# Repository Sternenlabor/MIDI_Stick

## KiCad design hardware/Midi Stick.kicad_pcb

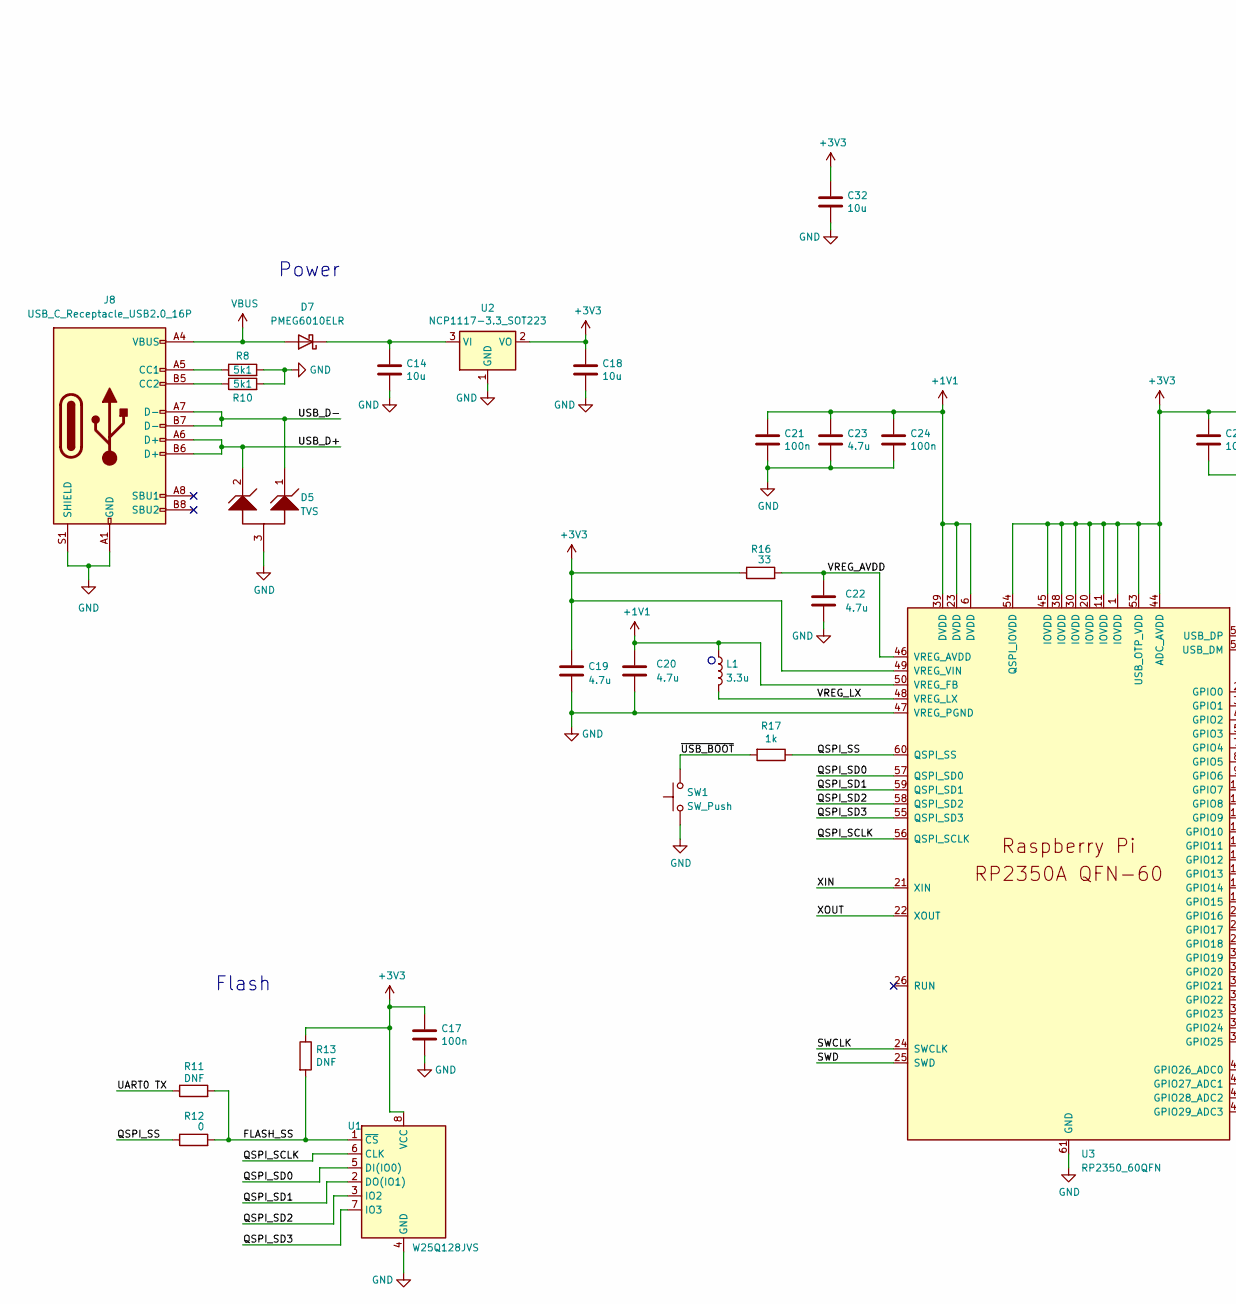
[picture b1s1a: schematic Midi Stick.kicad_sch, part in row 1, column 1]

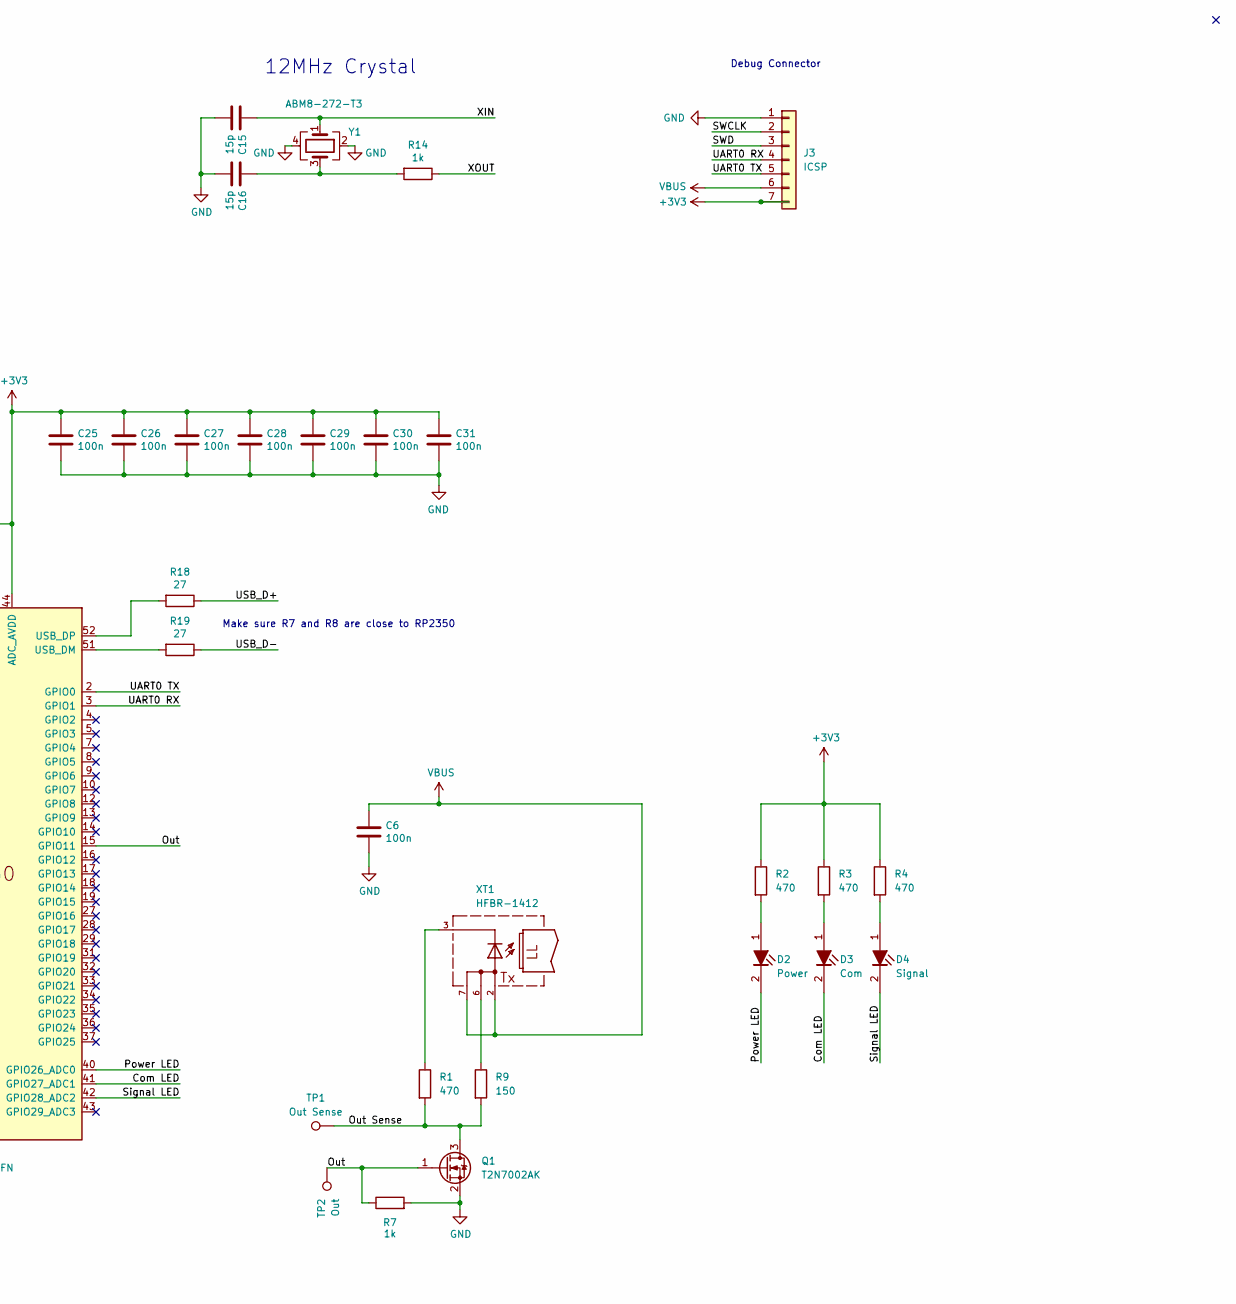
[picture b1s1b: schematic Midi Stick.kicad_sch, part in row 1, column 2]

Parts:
C6, C17, C21, C24, C25, C26, C27, C28, C29, C30, C31: 100n; C_0402_1005Metric
C14, C18, C32: 10u; C_0805_2012Metric
C15, C16: 15p; C_0402_1005Metric
C19, C20, C22, C23: 4.7u; C_0402_1005Metric
D2: Power; LED_0603_1608Metric
D3: Com; LED_0603_1608Metric
D4: Signal; LED_0603_1608Metric
D5: TVS; SOT95P230X110-3N
D7: PMEG6010ELR; D_SOD-123F
J3: ICSP; PinSocket_1x07_P2.54mm_Vertical
J8: USB_C_Receptacle_USB2.0_16P; USB_C_Receptacle_GCT_USB4105-xx-A_16P_TopMnt_Horizontal
L1: 3.3u; L_pol_2016
Q1: T2N7002AK; SOT-23
R1, R2, R3, R4: 470; R_0402_1005Metric
R7, R14, R17: 1k; R_0402_1005Metric
R8, R10: 5k1; R_0402_1005Metric
R9: 150; R_0402_1005Metric
R11, R13: DNF; R_0402_1005Metric
R12: 0; R_0402_1005Metric
R16: 33; R_0402_1005Metric
R18, R19: 27; R_0402_1005Metric
SW1: SW_Push; SW_Push_1P1T_NO_Vertical_Wuerth_434133025816
TP1: Out Sense; TestPoint_Pad_1.0x1.0mm
TP2: Out; PinHeader_1x01_P2.54mm_Vertical
U1: W25Q128JVS; SOIC-8_5.23x5.23mm_P1.27mm
U2: NCP1117-3.3_SOT223; SOT-223-3_TabPin2
U3: RP2350_60QFN; RP2350-QFN-60-1EP_7x7_P0.4mm_EP3.4x3.4mm_ThermalVias
XT1: HFBR-1412; HFBR-X41X; MPN HFBR-1412
Y1: ABM8-272-T3; Crystal_SMD_3225-4Pin_3.2x2.5mm

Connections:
+1V1: C20.1, C21.1, C23.1, C24.1, L1.1, U3.6 (DVDD), U3.23 (DVDD), U3.39 (DVDD), U3.50 (VREG_FB)
+3V3: C17.1, C18.1, C19.1, C25.1, C26.1, C27.1, C28.1, C29.1, C30.1, C31.1, C32.1, J3.7, R2.1, R3.1, R4.1, R13.1, R16.1, U1.8 (VCC), U2.2 (VO), U3.1 (IOVDD), U3.11 (IOVDD), U3.20 (IOVDD), U3.30 (IOVDD), U3.38 (IOVDD), U3.44 (ADC_AVDD), U3.45 (IOVDD), U3.49 (VREG_VIN), U3.53 (USB_OTP_VDD), U3.54 (QSPI_IOVDD); also elsewhere on the board
/Com LED: D3.2, U3.41 (GPIO27_ADC1)
/FLASH_SS: R11.2, R12.2, R13.2, U1.1 (~CS)
/Out: Q1.1 (G), R7.1, TP2.1, U3.15 (GPIO11)
/Out Sense: Q1.3 (D), R1.2, R9.2, TP1.1
/Power LED: D2.2, U3.40 (GPIO26_ADC0)
/QSPI_SCLK: U1.6 (CLK), U3.56 (QSPI_SCLK)
/QSPI_SD0: U1.5 (DI(IO0)), U3.57 (QSPI_SD0)
/QSPI_SD1: U1.2 (DO(IO1)), U3.59 (QSPI_SD1)
/QSPI_SD2: U1.3 (IO2), U3.58 (QSPI_SD2)
/QSPI_SD3: U1.7 (IO3), U3.55 (QSPI_SD3)
/QSPI_SS: R12.1, R17.1, U3.60 (QSPI_SS)
/SWCLK: J3.2, U3.24 (SWCLK)
/SWD: J3.3, U3.25 (SWD)
/Signal LED: D4.2, U3.42 (GPIO28_ADC2)
/UART0 RX: J3.4, U3.3 (GPIO1)
/UART0 TX: J3.5, R11.1, U3.2 (GPIO0)
/USB_D+: D5.2 (19), J8.A6 (D+), J8.B6 (D+), R18.1
/USB_D-: D5.1 (18), J8.A7 (D-), J8.B7 (D-), R19.1
/VREG_AVDD: C22.1, R16.2, U3.46 (VREG_AVDD)
/VREG_LX: L1.2, U3.48 (VREG_LX)
/XIN: C15.1, U3.21 (XIN), Y1.1
/XOUT: R14.1, U3.22 (XOUT)
/~USB_BOOT: R17.2, SW1.2
GND: C6.2, C14.2, C15.2, C16.2, C17.2, C18.2, C19.2, C20.2, C21.2, C22.2, C23.2, C24.2, C25.2, C26.2, C27.2, C28.2, C29.2, C30.2, C31.2, C32.2, D5.3 (20), J3.1, J8.A1 (GND), J8.A12 (GND), J8.B1 (GND), J8.B12 (GND), J8.S1 (SHIELD), Q1.2 (S), R7.2, R8.2, R10.2, SW1.1, U1.4 (GND), U2.1 (GND), U3.47 (VREG_PGND), U3.61 (GND), Y1.2, Y1.4; also elsewhere on the board
unnamed: C16.1, R14.2, Y1.3
unnamed: D2.1, R2.2
unnamed: D3.1, R3.2
unnamed: D4.1, R4.2
unnamed: C14.1, D7.1 (K), U2.3 (VI)
unnamed: J8.A5 (CC1), R8.1
unnamed: J8.B5 (CC2), R10.1
unnamed: R1.1, XT1.3
unnamed: R9.1, XT1.6
unnamed: R19.2, U3.51 (USB_DM)
unnamed: R18.2, U3.52 (USB_DP)
VBUS: C6.1, D7.2 (A), J3.6, J8.A4 (VBUS), J8.A9 (VBUS), J8.B4 (VBUS), J8.B9 (VBUS), XT1.2, XT1.7

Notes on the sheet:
Debug Connector
Make sure R7 and R8 are close to RP2350
Power
Flash
12MHz Crystal

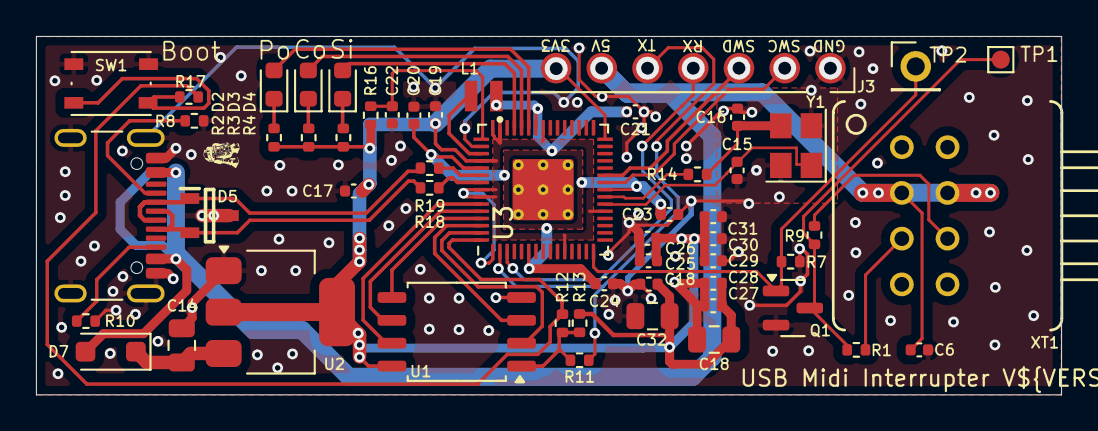
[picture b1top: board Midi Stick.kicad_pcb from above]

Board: 2 copper layers, 57.0 x 19.9 mm, 54 parts (0 on the bottom side), 38 nets.

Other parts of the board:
C18#2: 100n; C_0402_1005Metric

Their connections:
+3V3: C18#2.1; also elsewhere on the board
GND: C18#2.2; also elsewhere on the board

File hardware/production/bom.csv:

Designator,Footprint,Quantity,Value,LCSC Part #
"C14, C18_2, C32",0805,3,10u,
"C15, C16",0402,2,15p,
"C17, C18, C21, C24, C25, C26, C27, C28, C29, C30, C31, C6",0402,12,100n,
"C19, C20, C22, C23",0402,4,4.7u,
D2,0603,1,Power,
D3,0603,1,Com,
D4,0603,1,Signal,
D5,SOT95P230X110-3N,1,TVS,
D7,D_SOD-123F,1,PMEG6010ELR,
J3,PinSocket_1x07_P2.54mm_Vertical,1,ICSP,
J8,USB_C_Receptacle_GCT_USB4105-xx-A_16P_TopMnt_Horizontal,1,USB_C_Receptacle_USB2.0_16P,
L1,L_pol_2016,1,3.3u,
Q1,SOT-23,1,T2N7002AK,
"R1, R2, R3, R4",0402,4,470,
"R10, R8",0402,2,5k1,
R12,0402,1,0,
"R14, R17, R7",0402,3,1k,
R16,0402,1,33,
"R18, R19",0402,2,27,
R9,0402,1,150,
SW1,SW_Push_1P1T_NO_Vertical_Wuerth_434133025816,1,SW_Push,
TP1,TestPoint_Pad_1.0x1.0mm,1,Out Sense,
TP2,PinHeader_1x01_P2.54mm_Vertical,1,Out,
U1,SOIC-8_5.23x5.23mm_P1.27mm,1,W25Q128JVS,
U2,SOT-223-3_TabPin2,1,NCP1117-3.3_SOT223,
U3,RP2350-QFN-60-1EP_7x7_P0.4mm_EP3.4x3.4mm_ThermalVias,1,RP2350_60QFN,
XT1,HFBR-X41X,1,HFBR-1412,HFBR-1412
Y1,Crystal_SMD_3225-4Pin_3.2x2.5mm,1,ABM8-272-T3,

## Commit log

2024-06-27 converted from Altium to KiCad
2024-07-16 Fix recommended minimum PIC32 connection
2024-07-16 ignore KiCad backups
2024-07-16 add PIC32 data sheet
2024-07-17 added some notes
2024-07-26 fix some labels
2024-10-02 single sided
2024-10-02 layout update
2024-10-02 fix layout
2024-10-03 routing fixes
2025-06-28 move hardware into separate folder
2025-06-28 add test file
2025-06-28 commissioning firmware
2025-07-22 Added readme file and python test program to send midi notes.
2025-07-24 Cleanup hardware folder, schematic and PCB
2025-07-24 Fix LED Power issue

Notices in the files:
Midi Stick.kicad_sch:
Copyright (C) 2020,2021 TMax-Electronics.de
the MidiStick Project is free: you can redistribute it and/or modify
it under the terms of the GNU General Public License as published by
the Free Software Foundation, either version 3 of the License, or
(at your option) any later version.
